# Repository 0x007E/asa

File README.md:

# `ASA` - Audio Signal Amplifier

The `ASA` is a board with an [LM386](#additional-information) or any other audio signal amplifier. The board itself can be driven with a voltage between `5-12V`. It adds and amplifies the given  input signal(s) with a gain between `~50-200` to a connected speaker. If the supply of the board is available the `green` led is `on`. The board itself provides a reverse polarity protection.

| Experience | Level |
|:------------|:-----:|
| Soldering   |  |

# Downloads

| Type      | File               | Description              |
|:---------:|:------------------:|:-------------------------|
| Schematic | [pdf](https://github.com/0x007E/asa/releases/latest/download/schematic.pdf) / [cadlab](https://cadlab.io/project/30571/main/files) | Schematic files |
| Board | [pdf](https://github.com/0x007E/asa/releases/latest/download/pcb.pdf) / [cadlab](https://cadlab.io/project/30571/main/files) | Board file |
| Drill | [pdf](https://github.com/0x007E/asa/releases/latest/download/drill.pdf) | Drill file |
| BoM | [xlsx](https://github.com/0x007E/asa/releases/latest/download/bom.xlsx) / [html](https://github.com/0x007E/asa/releases/latest/download/ibom.html)          | Bill of Material as Excel/interactive HTML |
| PCB    | [zip](https://github.com/0x007E/asa/releases/latest/download/kicad.zip) / [tar](https://github.com/0x007E/asa/releases/latest/download/kicad.tar.gz)    | KiCAD/Gerber/BoM/Drill files       |

# Hardware

The pcb is created with `KiCAD`. All files are built with `github actions` so that they are ready for a production environment.

## PCB

The circuit board is populated on one side. The best way for soldering the `SMD` components is within a vapor phase soldering system and for the `THT` components with a standard system.

### Top Layer

### Bottom Layer

# Configuration

The gain of the `ASA` can be set with the `RV2` trimmer. If the trimmer is not solderd the standard gain is around `~20`. If `R7` and `C11` is solder `bass boost` mode is enabled.

# Additional Information

| Type  | Link                                               | Description                                 |
|:------|:--------------------------------------------------:|:--------------------------------------------|
| LM386 | [pdf](https://www.ti.com/lit/ds/symlink/lm386.pdf) | Low Voltage Audio Power Amplifier Datasheet |

---

R. GAECHTER

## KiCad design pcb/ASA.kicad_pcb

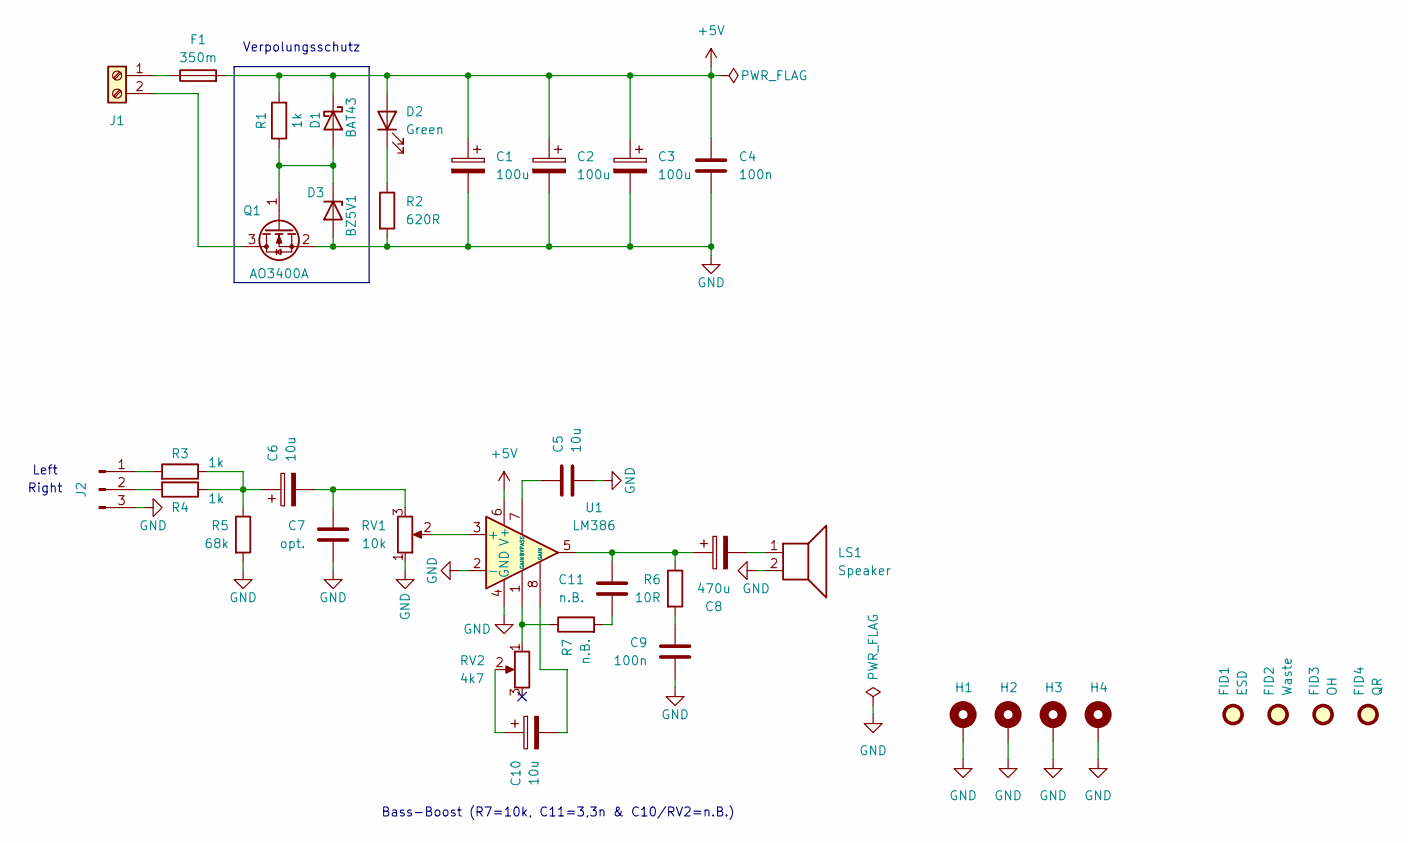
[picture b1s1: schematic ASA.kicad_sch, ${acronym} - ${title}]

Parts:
C1, C2, C3: 100u; CP_Radial_D5.0mm_P2.00mm
C4, C9: 100n; C_1206_3216Metric
C5: 10u; C_1206_3216Metric
C6, C10: 10u; CP_Elec_4x4.5
C7: opt.; C_1206_3216Metric
C8: 470u; CP_Radial_D8.0mm_P3.50mm
C11: n.B.; C_1206_3216Metric
D1: BAT43; D_MiniMELF
D2: Green; LED_1206_3216Metric
D3: BZ5V1; D_MiniMELF
F1: 350m; Fuse_1206_3216Metric
FID1: ESD; ESD-Logo_6.6x6mm_SilkScreen
FID2: Waste; WEEE-Logo_4.2x6mm_SilkScreen
FID3: OH; OSHW-Logo_5.7x6mm_SilkScreen
FID4: QR; QR_0x007e
H1, H2, H3, H4: MountingHole_Pad; MountingHole_3.2mm_M3_DIN965_Pad
J1: Screw_Terminal_01x02; TerminalBlock_Phoenix_MKDS-1,5-2-5.08_1x02_P5.08mm_Horizont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
J2: Conn_01x03_Pin; PinHeader_1x03_P2.54mm_Vertical
LS1: Speaker; TerminalBlock_Phoenix_MKDS-1,5-2-5.08_1x02_P5.08mm_Horizont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
Q1: AO3400A; SOT-23-3
R1, R3, R4: 1k; R_1206_3216Metric
R2: 620R; R_1206_3216Metric
R5: 68k; R_1206_3216Metric
R6: 10R; R_1206_3216Metric
R7: n.B.; R_1206_3216Metric
RV1: 10k; Potentiometer_Piher_PT-10-V10_Vertical
RV2: 4k7; Potentiometer_Bourns_3296W_Vertical
U1: LM386; DIP-8_W7.62mm_Socket_LongPads

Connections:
+5V: C1.1, C2.1, C3.1, C4.1, D1.1 (K), D2.2 (A), F1.2, R1.2, U1.6 (V+)
GND: C1.2, C2.2, C3.2, C4.2, C5.2, C7.2, C9.2, D3.2 (A), H1.1, H2.1, H3.1, H4.1, J2.3, LS1.2, Q1.2 (S), R2.2, R5.2, RV1.1, U1.2 (-), U1.4 (GND)
unnamed: C6.1, R3.1, R4.1, R5.1
unnamed: C6.2, C7.1, RV1.3
unnamed: C8.2, LS1.1
unnamed: C9.1, R6.2
unnamed: C10.1, RV2.2
unnamed: C10.2, U1.8 (GAIN)
unnamed: C8.1, C11.1, R6.1, U1.5
unnamed: C11.2, R7.2
unnamed: D1.2 (A), D3.1 (K), Q1.1 (G), R1.1
unnamed: D2.1 (K), R2.1
unnamed: F1.1, J1.1
unnamed: J1.2, Q1.3 (D)
unnamed: J2.1, R3.2
unnamed: J2.2, R4.2
unnamed: R7.1, RV2.1, U1.1 (GAIN)
unnamed: RV1.2, U1.3 (+)
unnamed: C5.1, U1.7 (BYPASS)

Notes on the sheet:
Verpolungsschutz
Right
Bass-Boost (R7=10k, C11=3,3n & C10/RV2=n.B.)
Left

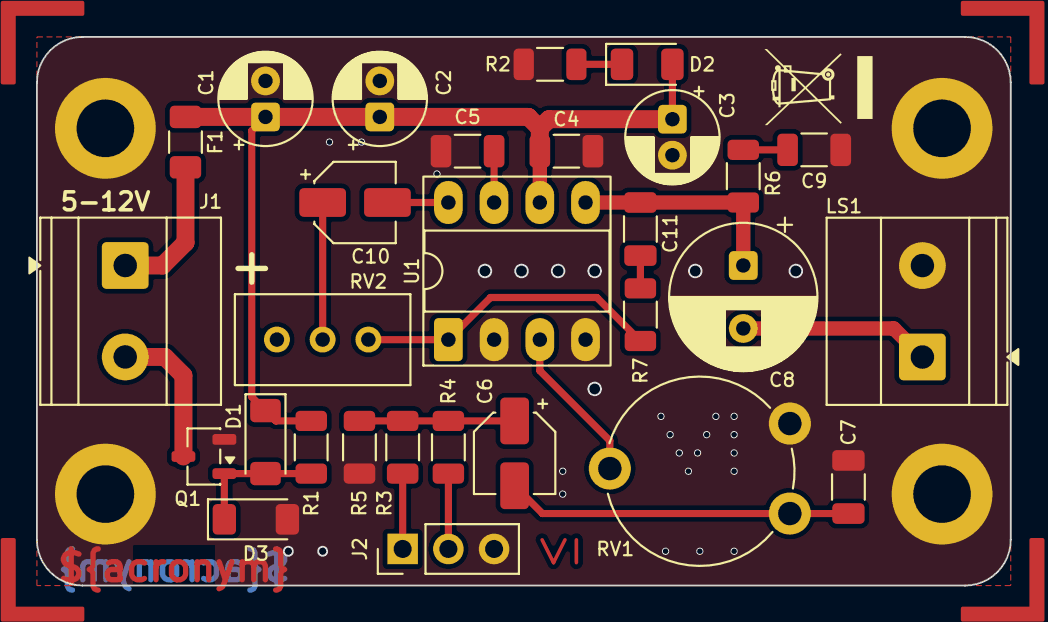
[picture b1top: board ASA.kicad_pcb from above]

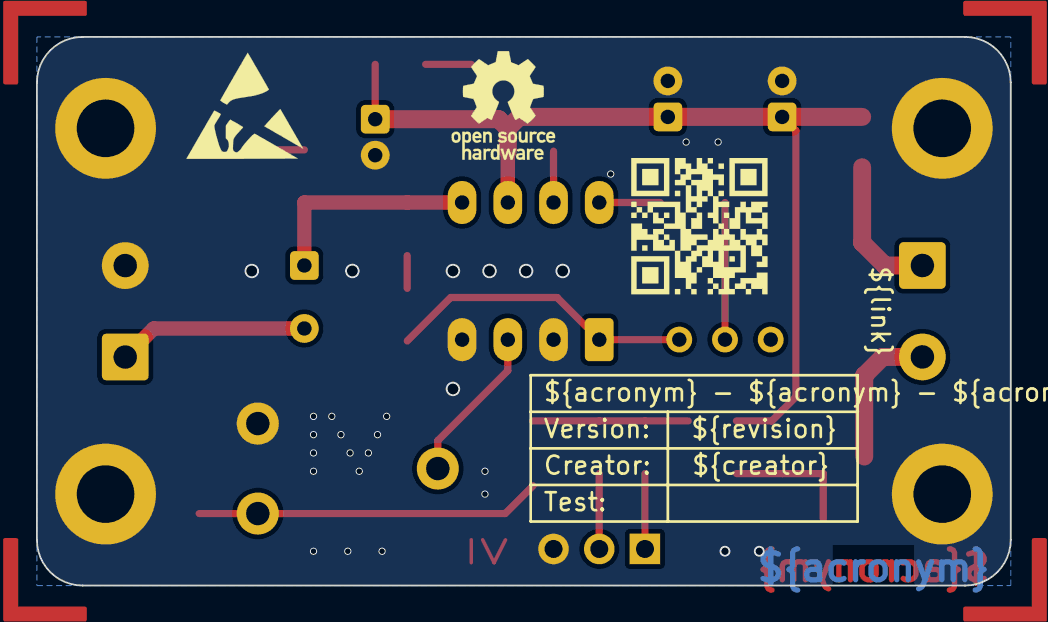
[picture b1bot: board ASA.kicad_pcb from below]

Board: 2 copper layers, 54.1 x 30.5 mm, 37 parts (3 on the bottom side), 19 nets.

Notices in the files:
README.md:
License CC By-NC-SA
parts and their libraries:
license: CC BY-NC-SA 4.0
